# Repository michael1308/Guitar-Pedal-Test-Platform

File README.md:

# Guitar Pedal Test Platform
A simple interface board for testing and developing guitar pedals

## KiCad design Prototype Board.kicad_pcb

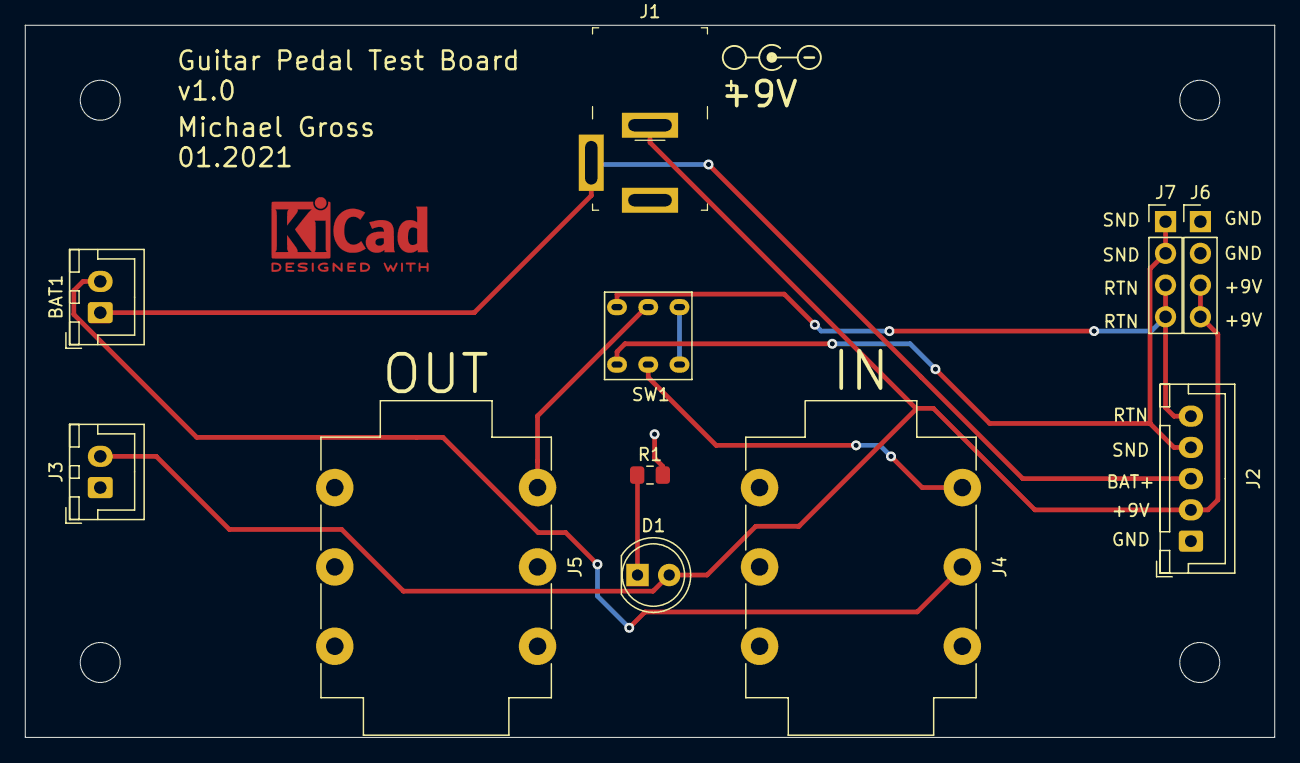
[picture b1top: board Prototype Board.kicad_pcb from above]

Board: 2 copper layers, 100.0 x 57.0 mm, 11 parts (0 on the bottom side), 10 nets.

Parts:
BAT1: Conn_01x02_Female; JST_XH_B2B-XH-A_1x02_P2.50mm_Vertical
D1: LED; LED_D5.0mm
J1: Barrel_Jack_Switch; Barrel_Jack_5.5mmODx2.1mmID_PJ-202A
J2: Conn_01x05_Female; JST_XH_B5B-XH-A_1x05_P2.50mm_Vertical
J3: Conn_01x02_Female; JST_XH_B2B-XH-A_1x02_P2.50mm_Vertical
J4, J5: AudioJack3_Switch; Jack_6.35mm_Neutrik_NMJ6HCD2_Horizontal
J6, J7: Conn_01x04_Female; PinHeader_1x04_P2.54mm_Vertical
R1: R; R_0805_2012Metric_Pad1.15x1.40mm_HandSolder
SW1: SW_DPDT_x2; DPDT Latching Push Switch 7x7

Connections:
+9V: D1.2, J1.2, J2.2, J3.2, J6.3, J6.4
BAT+: BAT1.1, J1.3, J2.3
BAT-: BAT1.2, J4.R
GND: J1.1, J2.1, J3.1, J4.S, J5.S, J6.1, J6.2, R1.2
IN: J4.T, SW1.2
unnamed: D1.1, R1.1
unnamed: SW1.3, SW1.6
OUT: J5.T, SW1.5
RTN: J2.5, J7.3, J7.4, SW1.4
SND: J2.4, J7.1, J7.2, SW1.1

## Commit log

2024-02-22 Initial commit.
